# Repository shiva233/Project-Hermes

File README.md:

# Project Hermes 

> Hermes (n.): God of speed, travel, and messangers. In this incarnation he carries pixels instead of scrolls, streaming your games from your desktop to your hands :D

## LIVE DEMO (check replies)
https://x.com/shiva233233/status/1951108410113454563?s=46

## What is Project Hermes?
Project Hermes is a Raspberry Pi powered game _**streaming**_ handheld built for PC gamers, streaming your games from your pc via SteamLink to the console wherever you want! (provided you have an internet connection) and since its only streaming the games you can do this without rebuying games or paying console prices for the hardware! 

## Why did I make Project Hermes

This might sound silly but I made Project Hermes because... I really really really want it! I want something like this to use! All the handheld consoles on the market right now are way to expensive and besides that I have two big issues with all of them:

1. I can't play on the same save file as my main computer on the handheld (without some tedious work around)
2. I already have a good pc! why should I a lot of money for a handheld to run the same games slightly worse??

So I designed a handheld that fixes both of these issues! It streams directly from the main PC so all the save files are still stored on the main computer, and since its running of the main computers hardware the console can be cheaper and use less expensive hardware! The whole thing pretty much runs of a Raspberry Pi 4 and is in total cheaper than a Switch Lite :D

## Design Constraints / Goals:

- Size: Must be similar size/footprint to Steam Deck, ROG Ally or Switch (around 30cm x 11cm x 4cm) ☑️ (well... except for that 4cm part it ended up being a lil bit more chonky lol!!)
- Price: Must be cheaper than a Switch Lite (since it can't actually run games natively and only stream its not reasonable for it to cost more than an actual console) therefore must cost less than **$260 CAD or $190 USD** ☑️
- Power: Battery Powered, chargable via USB-C while in use (aiming for around 2-3 hours) ☑️
- Compute: Be able to run SteamLink at 720p 60hz ☑️
- Display: Atleast 7 inch, 720p 60hz, HDMI compatible ☑️
- Input: Via USB HID, same layout as an Xbox controller ☑️
- Connectivity: Must be able to run off just WiFi ☑️ 
- Encolosure: Fully 3D Printed, no custom fabrication or CNC. Easily assembled with hand tools ☑️

## Anatomy of Project Hermes:

Raspberry Pi 4 (2 GB with cooler) + Pisugar S Pro Portable 5000 mAh UPS +  7 inch LCD Display + RP2040-Zero Custom Controller + 3D Printed Housing = Project Hermes! :D 

## 3D Model

## Controller PCB:

## Wiring / Cable fun

Display: Hdmi to Micro Hdmi + Power mico-usb that both plug into the Pi

Controller: USB-C to USB-A that plugs into the Pi

Battery: its a hat! 

Shoulder Buttons: Shoulder buttons may be hand wired to the PCB with a wire extending it :O

## Firmware

ok this part is important and might be confusing, Project Hermes uses two layers of firmware/software:

### 1. Raspberry Pi 4 - [SteamLink](https://store.steampowered.com/app/353380/Steam_Link/) Client

The Raspberry Pi 4 will be running [Raspberry Pi OS](https://www.raspberrypi.com/software/operating-systems/) with the official [SteamLink](https://store.steampowered.com/app/353380/Steam_Link/) client downloaded onto it (might also add a script that makes SteamLink automatically launch every time the Pi is booted :0).

SteamLink Handles this:

- Video/Audio: It takes the video and audio from your computer and streams it to the Pi!
- It also takes inputs from the controller on Project Hermes and sends it back to your computer

So basically:

Gaming PC => SteamLink => Project Hermes (Video + Audio)

Project Hermes => SteamLink => Gaming PC (Controller Input)

This makes it so all the heavy lifting/processing power is done by your PC and the Pi just becomes the bridge the carries the pixels (video/audio) in one direction and controller signals in the other (just like Hermes!!).

### 2. Custom Controller - [GP2040-CE Firmware](https://github.com/OpenStickCommunity/GP2040-CE)

- The RP2040-Zero microcontroller inside the controller PCB will be running [GP2040-CE, which is an opensource firmware deisnged for game controllers! ](https://github.com/OpenStickCommunity/GP2040-CE)
What GP2040-CE does:
- Turns the controller into a USB HID! Basically this means that the Pi and PC see it as a standard controller just like an Xbox controller
- Handles all the button presses, D-pad inputs, and analog signals from the joysticks (which the Pi cannot do btw since it does not have analog pins to my knowledge) and then sends them as input data over USB to the Pi.
- It's low latency and fully compatible with SteamLink, which means your computer treats Project Hermes like a normal controller with no special drivers or extra setup :D
- LOOK INTO GP2040-CE AND SUPPORT THEM THEY ARE SO COOL RAHHHH >:O

Why This Setup?

- No custom firmware: Since GP2040-CE is highly optimized for gaming responsiveness (fancy shamncy way of saying its low latency ig) and supports all the features I need for this project without :DD
- Plug and play: this one is kinda self explantory but it makes sure that I can just plug in USB and immediately start using it as a controller without having the Raspberry Pi guess what the controller is or anything like that
- Reliability: Using a seperate dedicated microcontroller for the input reduces latency and avoids weird input issues (take this with a grain of salt this is what I infered from other handheld console projects online) 

## BOM

| Item                                | Usage                        | Source       | Link                                        | Price (CAD) |
|-------------------------------------|------------------------------|--------------|---------------------------------------------|-------------|
| Raspberry Pi 4 (2 GB)               | Computer                     | AliExpress   |           https://a.aliexpress.com/_mrh0oph |      $80.38 |
| Pi 4 Cooling Fan                    | Cooling                      | Ali Express  |           https://a.aliexpress.com/_mOZZjXv |       $5.67 |
| Pisugar S Pro Portable 5000 mAh UPS | Power Supply / Bank          | Amazon       | https://www.amazon.ca/gp/product/B097RCFHD2 |      $47.46 |
| 7 inch LCD Display                  | Display                      | AliExpress   |           https://a.aliexpress.com/_mPIB3Jt |      $34.99 |
| Waveshare rp2040-Zero               | Controller Microcontroller   | Self-Sourced |                                         N/a |       $0.00 |
| Tact Switch Push Button             | Controller Buttons + Trigger | AliExpress   |           https://a.aliexpress.com/_mMydiq7 |       $2.42 |
| Analog Joysticks                    | Controller Joysticks         | AliExpress   |           https://a.aliexpress.com/_mNbLpIn |       $4.33 |
| Controller PCB                      | Controller PCB               | JLCPCB       |                                         N/a |      $25.76 |
| 3D Printed Case/Parts               | Housing/Buttons              | Self-Sourced |                                         N/a |       $0.00 |
|                                     |                              |              |                                   Total CAD |     $201.01 |
|                                     |                              |              |                                   Total USD |     $146.74 |

Note: the pisugar was cheaper on amazon than aliexpress
(that's cheaper than a Switch Lite :O)

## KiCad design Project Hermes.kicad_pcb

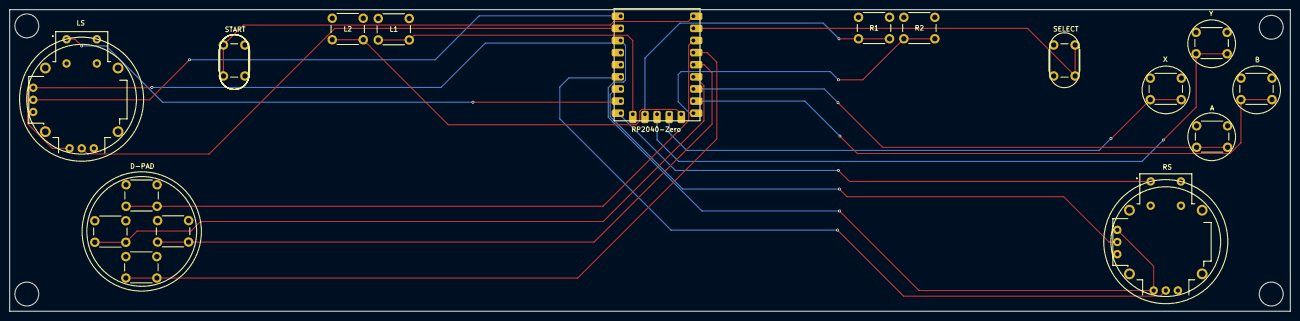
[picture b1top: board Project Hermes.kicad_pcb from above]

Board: 2 copper layers, 268.4 x 63.2 mm, 17 parts (0 on the bottom side), 22 nets.

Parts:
A: SW_Push; SW_PUSH_6mm
B: SW_Push; SW_PUSH_6mm
D-PAD: SW_Push; SW_PUSH_6mm
DOWN1: SW_Push; SW_PUSH_6mm
L1, L2: SW_Push; SW_PUSH_6mm
LEFT1: SW_Push; SW_PUSH_6mm
LS: COM-09032; XDCR_COM-09032
R1, R2: SW_Push; SW_PUSH_6mm
RIGHT1: SW_Push; SW_PUSH_6mm
RS: COM-09032; XDCR_COM-09032
RZ1: RP2040-Zero
SELECT: SW_Push; SW_PUSH_6mm
START: SW_Push; SW_PUSH_6mm
X: SW_Push; SW_PUSH_6mm
Y: SW_Push; SW_PUSH_6mm

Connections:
/GP00: RZ1.1 (GP0), START.2
/GP01: RZ1.2 (GP1), SELECT.2
/GP02: D-PAD.2, RZ1.3 (GP2)
/GP03: DOWN1.2, RZ1.4 (GP3)
/GP04: RIGHT1.2, RZ1.5 (GP4)
/GP05: LEFT1.2, RZ1.6 (GP5)
/GP06: A.2, RZ1.7 (GP6)
/GP07: B.2, RZ1.8 (GP7)
/GP08: R2.2, RZ1.9 (GP8)
/GP09: L2.2, RZ1.10 (GP9)
/GP10: RZ1.11 (GP10), X.2
/GP11: RZ1.12 (GP11), Y.2
/GP12: R1.2, RZ1.13 (GP12)
/GP13: L1.2, RZ1.14 (GP13)
/GP14: RS.B1A (SEL+), RZ1.15 (GP14)
/GP15: LS.B1A (SEL+), RZ1.16 (GP15)
/GP26: RS.V2 (V), RZ1.17 (GP26)
/GP27: RS.H2 (H), RZ1.18 (GP27)
/GP28: LS.V2 (V), RZ1.19 (GP28)
/GP29: LS.H2 (H), RZ1.20 (GP29)
GND: A.1, B.1, D-PAD.1, DOWN1.1, L1.1, L2.1, LEFT1.1, LS.B2A (SEL-), LS.H3 (H-), LS.V3 (V-), R1.1, R2.1, RIGHT1.1, RS.B2A (SEL-), RS.H3 (H-), RS.V3 (V-), RZ1.23 (GND), SELECT.1, START.1, X.1, Y.1
VCC: LS.H1 (H+), LS.V1 (V+), RS.H1 (H+), RS.V1 (V+), RZ1.21 (3V3)

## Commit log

2025-07-26 Rename Project Hermes.kicad_pro to PCB/Project Hermes.kicad_pro
2025-07-26 Rename Project_Hermes.zip to PCB/Project_Hermes.zip
2025-07-26 Create temp
2025-07-26 Update and rename Project Hermes - BOM - Sheet1.csv to BOM
2025-07-26 Update BOM
2025-07-26 Rename Project Hermes v52.f3z to CAD/Project Hermes v52.f3z
2025-07-26 Rename Project Hermes v52.stl to CAD/Project Hermes v52.stl
